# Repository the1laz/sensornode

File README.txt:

Wireless sensor node hardware designed for nRF24L01 radios.

Model A is a node for an Atmega328.

Tabs are addon boards that connect to one of the 10 pin headers.

More information and pictures can be found on my blog: http://www.addictedtopi.com

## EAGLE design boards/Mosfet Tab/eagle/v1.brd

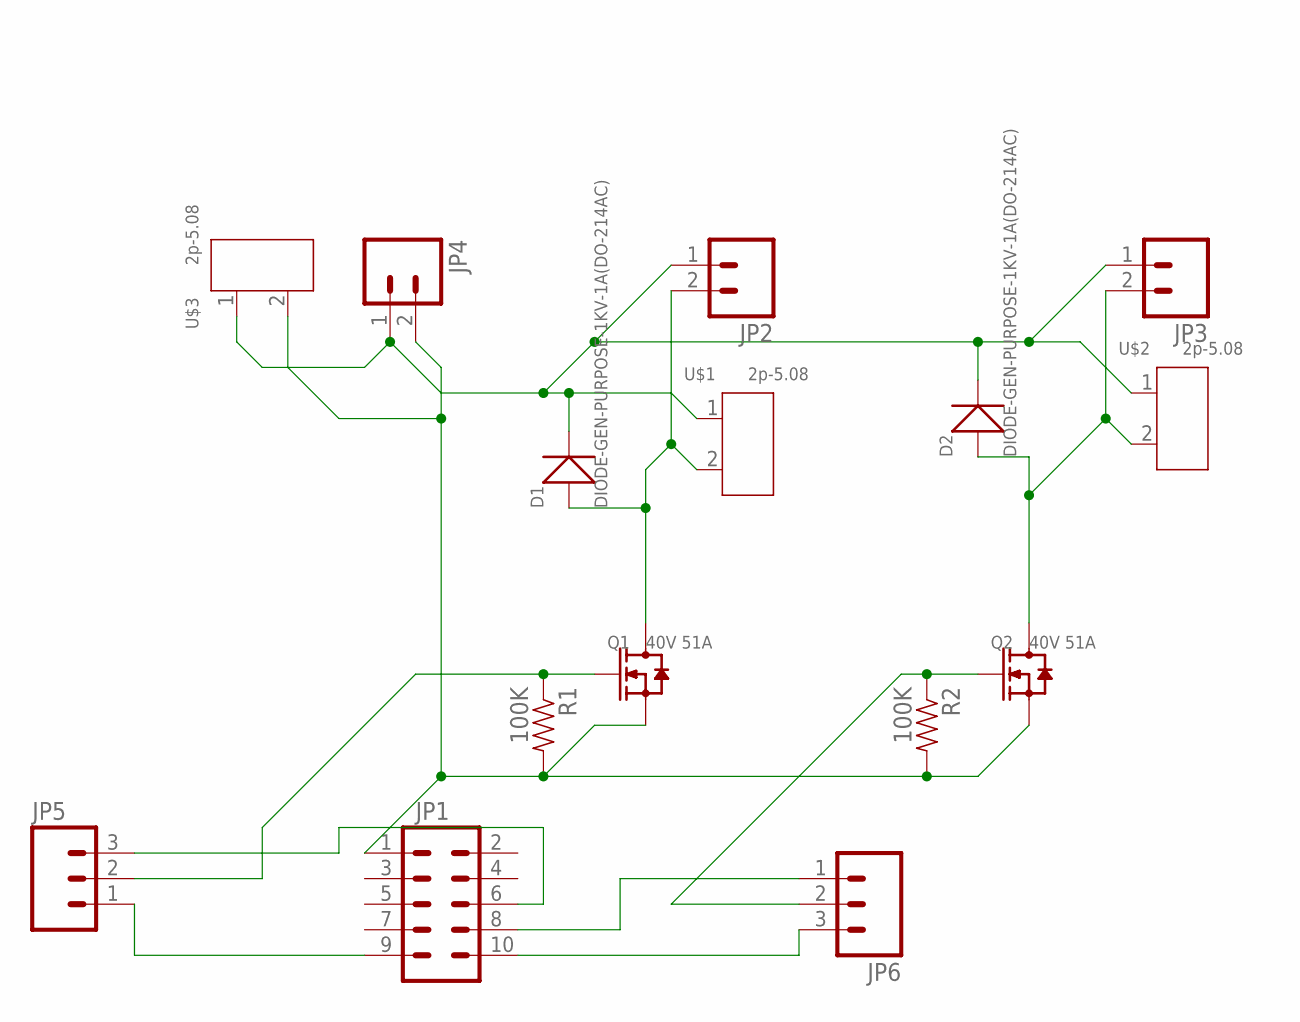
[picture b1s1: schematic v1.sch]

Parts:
D1, D2: DIODE-GEN-PURPOSE-1KV-1A(DO-214AC); DO-214AC
JP1: M05X2PTH; AVR_ICSP
JP2, JP3, JP4: M02POLAR; MOLEX-1X2
JP5, JP6: M03PTH; 1X03
Q1, Q2: 40V 51A; DPAK
R1, R2: 100K; 0805
U$1, U$2, U$3: 2p-5.08; H2-5.0-10.5X8.0MM

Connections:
GND: JP1.1, JP4.2, Q1.2 (S), Q2.2 (S), R1.2, R2.2, U$3.2
unnamed: D1.2 (-), D2.2 (-), JP2.1, JP3.1, JP4.1, U$1.1, U$2.1, U$3.1
unnamed: D2.1 (+), JP3.2, Q2.3 (D), U$2.2
unnamed: D1.1 (+), JP2.2, Q1.3 (D), U$1.2
unnamed: JP5.2, Q1.1 (G), R1.1
unnamed: JP6.2, Q2.1 (G), R2.1
unnamed: JP1.9, JP5.1
unnamed: JP1.10, JP6.3
unnamed: JP1.6, JP5.3
unnamed: JP1.8, JP6.1

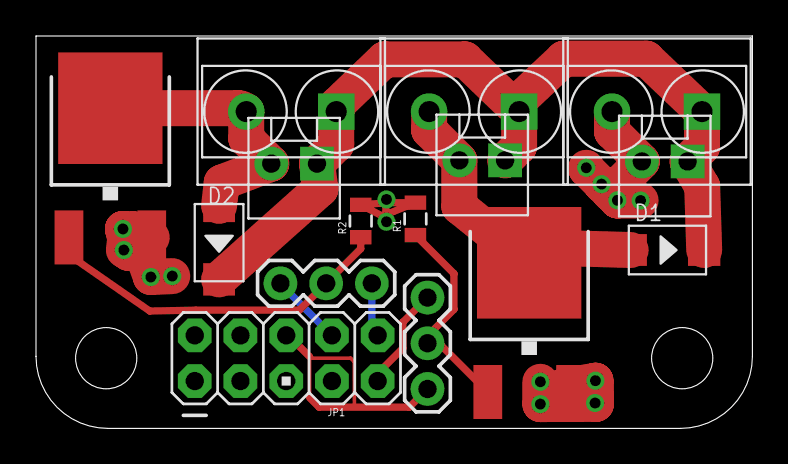
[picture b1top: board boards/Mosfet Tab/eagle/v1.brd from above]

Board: 2 copper layers, 39.8 x 21.8 mm, 15 parts (0 on the bottom side), 10 nets.

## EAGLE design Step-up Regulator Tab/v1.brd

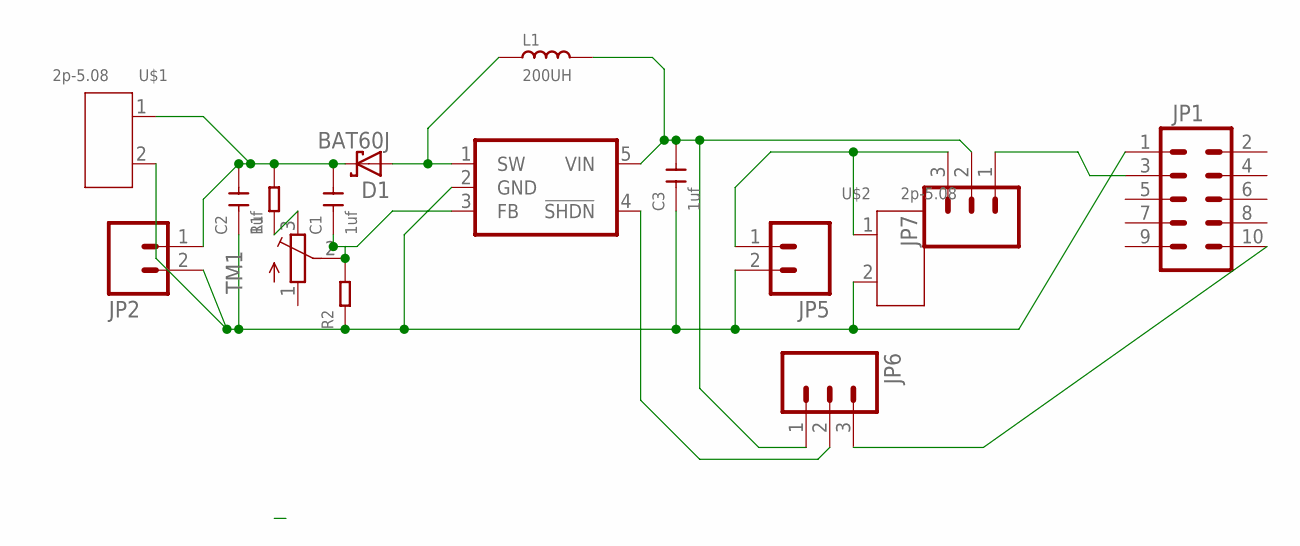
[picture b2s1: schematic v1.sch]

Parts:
C1, C2, C3: 1uf; C0805
D1: BAT60J; SOD323_ST
IC1: IC_FAN5331-SOT-23-5; SOT-23-5
JP1: M05X2PTH; AVR_ICSP
JP2, JP5: M02PTH; 1X02
JP6, JP7: M03PTH; 1X03
L1: 200UH; SMD-2P-5.0X5.0X2.0MM
R1, R2: RES-0805; R0805
TM1: TRIMPOTTC33X; TC33X
U$1, U$2: 2p-5.08; H2-5.0-10.5X8.0MM

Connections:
GND: C2.1, C3.1, IC1.2 (GND), JP1.1, JP2.2, JP5.2, R2.1, U$1.2, U$2.2
unnamed: JP1.3, JP7.1
unnamed: C3.2, IC1.5 (VIN), JP6.1, JP7.2, L1.2
unnamed: IC1.4 (!SHDN), JP6.2
unnamed: JP1.10, JP6.3
unnamed: D1.A, IC1.1 (SW), L1.1
unnamed: C1.2, C2.2, D1.C, JP2.1, R1.2, U$1.1
unnamed: C1.1, IC1.3 (FB), R2.2, TM1.2 (S)
unnamed: JP5.1, JP7.3, U$2.1
unnamed: R1.1, TM1.3 (E)

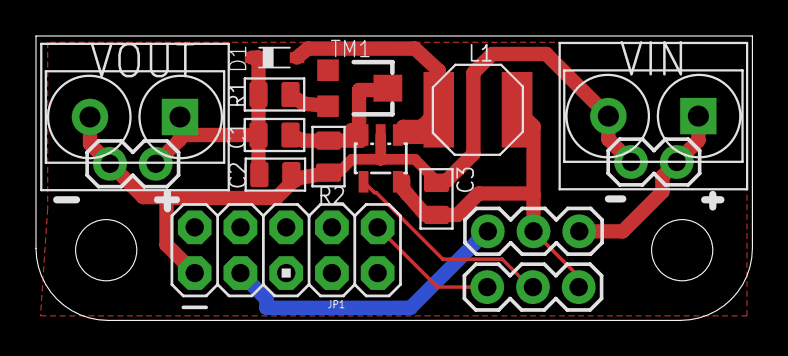
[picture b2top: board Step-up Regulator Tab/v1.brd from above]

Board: 2 copper layers, 39.8 x 15.8 mm, 16 parts (0 on the bottom side), 10 nets.

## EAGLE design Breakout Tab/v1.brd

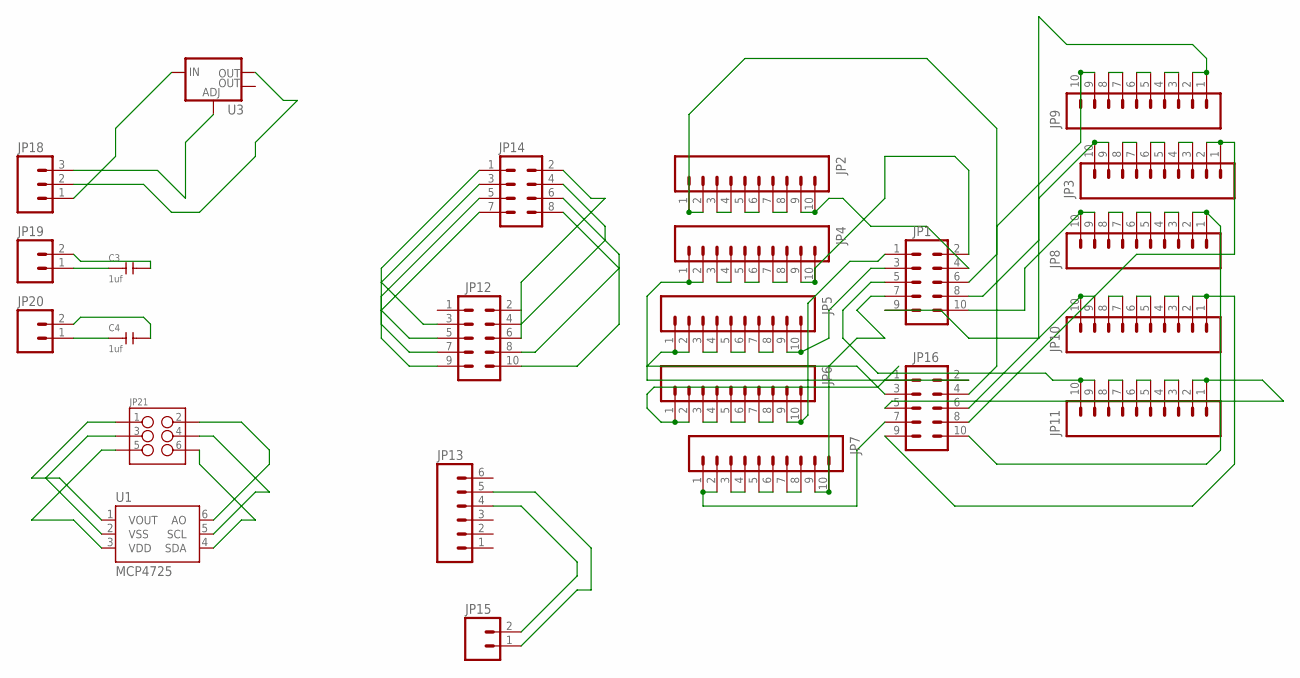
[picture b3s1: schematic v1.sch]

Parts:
C3, C4: 1uf; C0805
JP1, JP12, JP16: M05X2PTH; AVR_ICSP
JP2, JP3, JP4, JP5, JP6, JP7, JP8, JP9, JP10, JP11: M10SILK_FEMALE_PTH; 1X10
JP13: M06SILK_FEMALE_PTH; 1X06
JP14: M04X2; 2X4
JP15, JP19, JP20: M02PTH; 1X02
JP18: M03PTH; 1X03
JP21: M03X22X3_SILK_MALE_PTH; 2X3
U1: MCP4725; SOT23-6
U3: V_REG_LM1117SOT223; SOT223

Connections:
unnamed: JP2.3, JP2.4
unnamed: JP1.2, JP4.9, JP4.10
unnamed: JP1.3, JP5.9, JP5.10
unnamed: JP1.1, JP6.9, JP6.10
unnamed: JP1.9, JP10.9, JP10.10
unnamed: JP1.5, JP11.9, JP11.10
unnamed: JP3.1, JP3.2, JP16.8
unnamed: JP1.8, JP3.9, JP3.10
unnamed: JP1.7, JP7.9, JP7.10
unnamed: JP1.6, JP9.9, JP9.10
unnamed: JP9.7, JP9.8
unnamed: JP9.5, JP9.6
unnamed: JP9.3, JP9.4
unnamed: JP9.1, JP9.2, JP16.6
unnamed: JP3.7, JP3.8
unnamed: JP3.5, JP3.6
unnamed: JP3.3, JP3.4
unnamed: JP21.2, U1.6 (AO)
unnamed: JP10.1, JP10.2, JP16.9
unnamed: JP8.3, JP8.4
unnamed: JP8.5, JP8.6
unnamed: JP8.7, JP8.8
unnamed: JP11.7, JP11.8
unnamed: JP11.5, JP11.6
unnamed: JP11.3, JP11.4
unnamed: JP6.1, JP6.2, JP16.1
unnamed: JP21.4, U1.5 (SCL)
unnamed: JP10.3, JP10.4
unnamed: JP10.5, JP10.6
unnamed: JP10.7, JP10.8
unnamed: JP5.7, JP5.8
unnamed: JP5.5, JP5.6
unnamed: JP5.1, JP5.2, JP16.3
unnamed: JP5.3, JP5.4
unnamed: JP21.6, U1.4 (SDA)
unnamed: JP6.3, JP6.4
unnamed: JP6.5, JP6.6
unnamed: JP6.7, JP6.8
unnamed: JP7.1, JP7.2, JP16.7
unnamed: JP7.3, JP7.4
unnamed: JP7.5, JP7.6
unnamed: JP7.7, JP7.8
unnamed: JP4.1, JP4.2, JP16.2
unnamed: JP4.3, JP4.4
unnamed: JP4.5, JP4.6
unnamed: JP4.7, JP4.8
unnamed: JP11.1, JP11.2, JP16.5
unnamed: JP2.7, JP2.8
unnamed: JP2.5, JP2.6
unnamed: JP2.1, JP2.2, JP16.4
unnamed: JP1.10, JP8.9, JP8.10
unnamed: JP21.5, U1.3 (VDD)
unnamed: JP21.3, U1.2 (VSS)
unnamed: JP1.4, JP2.9, JP2.10
unnamed: JP13.4, JP15.2
unnamed: JP13.5, JP15.1
unnamed: JP12.4, JP14.2
unnamed: JP12.6, JP14.4
unnamed: JP12.8, JP14.6
unnamed: JP12.10, JP14.8
unnamed: JP12.3, JP14.1
unnamed: JP12.5, JP14.3
unnamed: JP12.7, JP14.5
unnamed: JP12.9, JP14.7
unnamed: JP21.1, U1.1 (VOUT)
unnamed: JP18.3, U3.1 (ADJ)
unnamed: JP8.1, JP8.2, JP16.10
unnamed: C3.1, JP19.1
unnamed: C3.2, JP19.2
unnamed: C4.1, JP20.1
unnamed: C4.2, JP20.2
unnamed: JP18.2, U3.2 (OUT)
unnamed: JP18.1, U3.3 (IN)

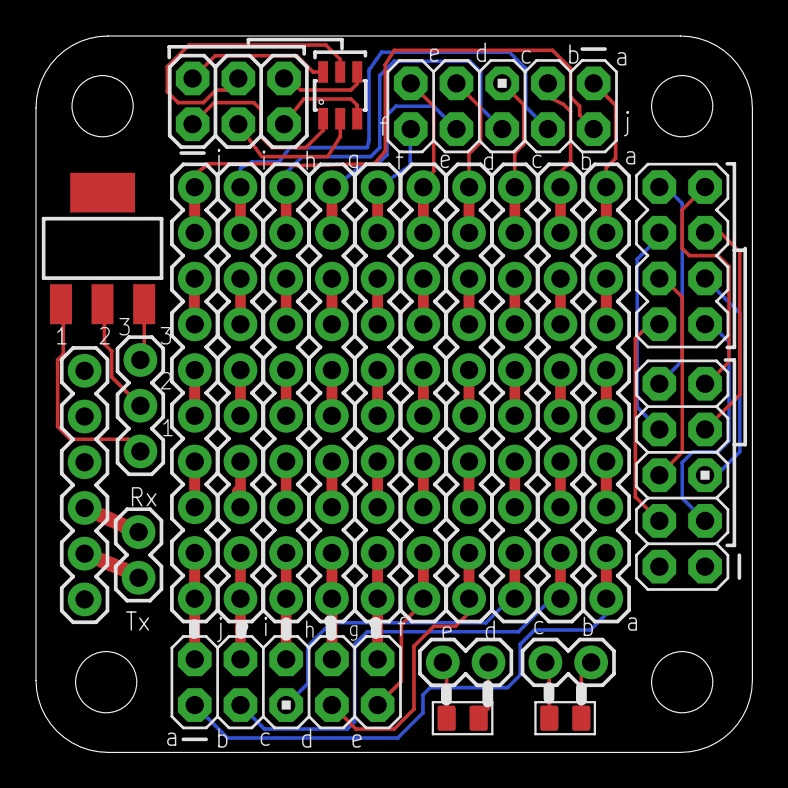
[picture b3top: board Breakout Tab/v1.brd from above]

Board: 2 copper layers, 39.8 x 39.8 mm, 24 parts (0 on the bottom side), 73 nets.

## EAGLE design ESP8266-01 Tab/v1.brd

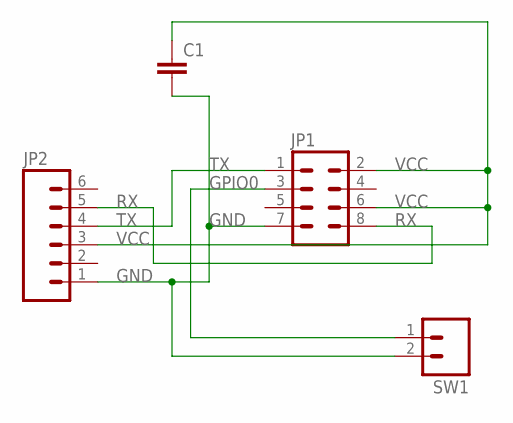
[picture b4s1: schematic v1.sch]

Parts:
C1: CAPPTH; CAP-PTH-SMALL
JP1: M04X2; 2X4
JP2: M06SILK_FEMALE_PTH; 1X06
SW1: M02PTH; 1X02

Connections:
GND: C1.2, JP1.7, JP2.1, SW1.2
GPIO0: JP1.3, SW1.1
RX: JP1.8, JP2.5
TX: JP1.1, JP2.4
VCC: C1.1, JP1.2, JP1.6, JP2.3

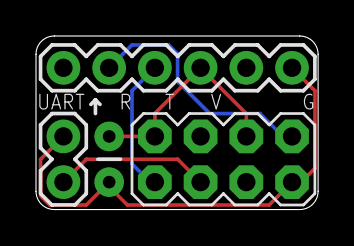
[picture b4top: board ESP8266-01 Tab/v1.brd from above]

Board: 2 copper layers, 15.7 x 9.6 mm, 4 parts (0 on the bottom side), 5 nets.

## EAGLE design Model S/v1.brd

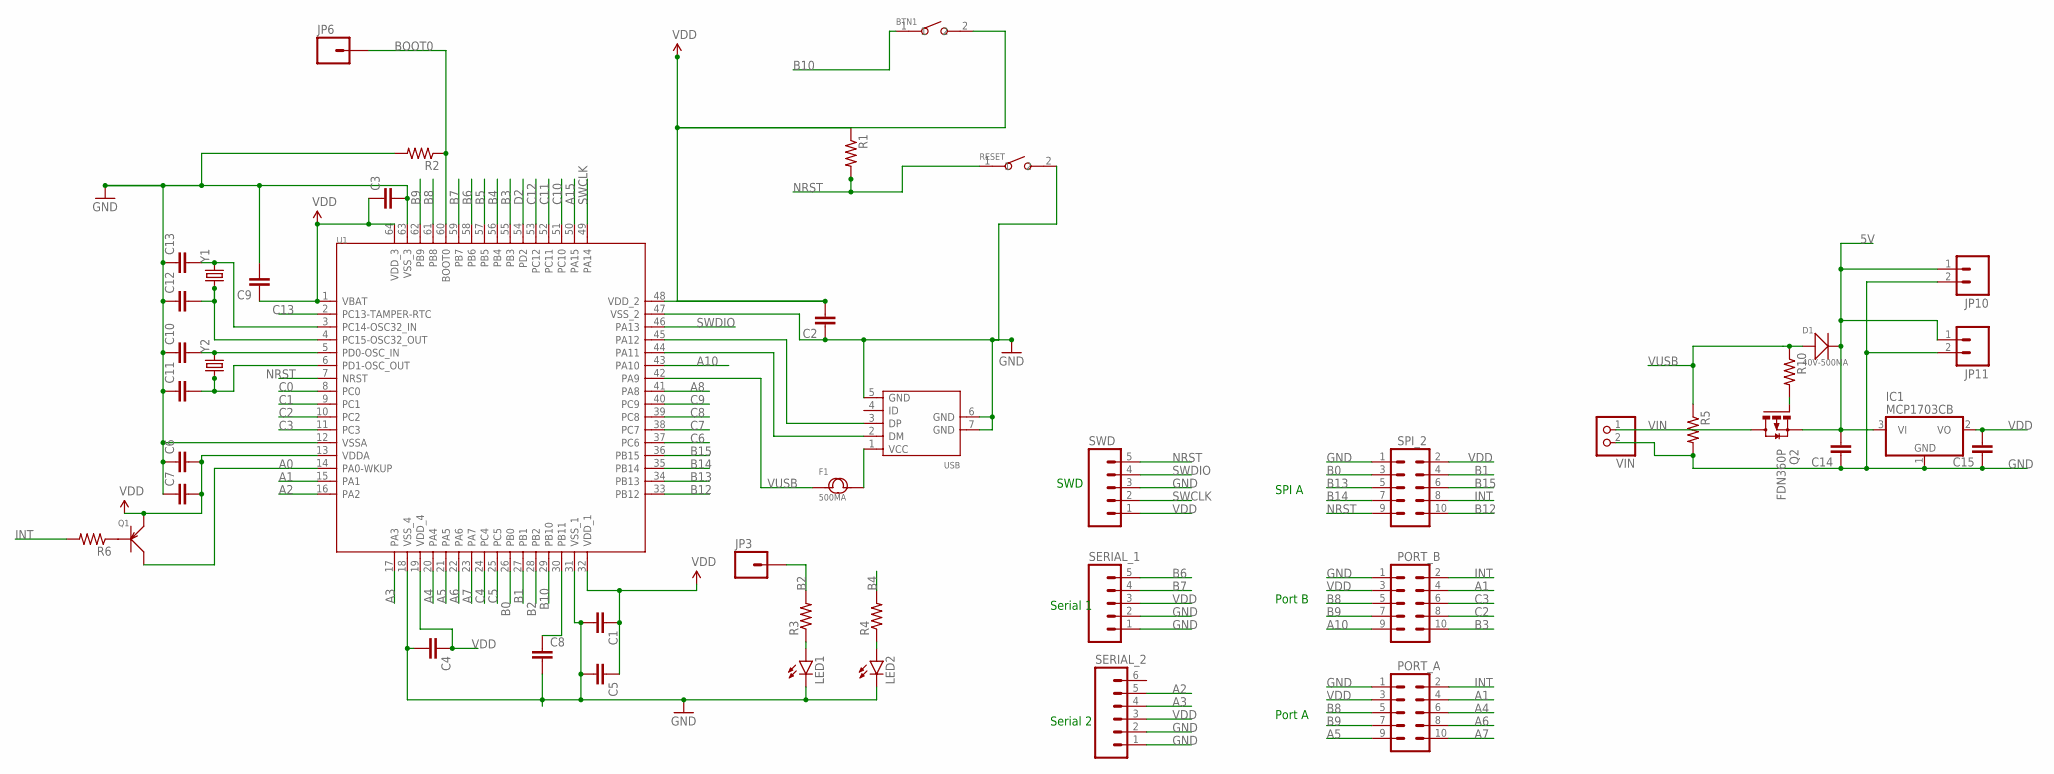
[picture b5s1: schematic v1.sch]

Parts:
BTN1: SMD-BUTTON(2P-6.0X3.0X2.5MM)-DHT-1163S; SW2-4.0-6.0X3.0X2.5MM
C1, C2, C3, C4, C5, C6, C7, C8, C9, C10, C11, C12, C13, C14, C15: CAP0805; 0805
D1: 40V-500MA; SOD-123
F1: 500MA; F1206
IC1: MCP1703CB; SOT23
JP3, JP6: M01NOSILK-KIT; 1X01NS-KIT
JP10, JP11: M02PTH; 1X02
LED1, LED2: LED1206; LED-1206
PORT_A: M05X2PTH; AVR_ICSP
PORT_B: M05X2PTH; AVR_ICSP
Q1: SMD-TRANSISTORS-PNP-25V-500MA(SOT-23); SOT-23
Q2: FDN360P; SUPER-SOT3
R1, R2, R3, R4, R5, R6, R10: RESISTOR0805-RES; 0805
RESET: SMD-BUTTON(2P-6.0X3.0X2.5MM)-DHT-1163S; SW2-4.0-6.0X3.0X2.5MM
SERIAL_1: M051.27MM; 1X05-1.27MM
SERIAL_2: M06SILK_FEMALE_PTH; 1X06
SPI_2: M05X2PTH; AVR_ICSP
SWD: M051.27MM; 1X05-1.27MM
U1: MCU-STM32F401RBT6(LQFP64); LQFP64-0.5-10X10MM
USB: MICRO-USB-SMD-TYPE-AB-R/A(ST-USB-001L); MICRO-USB5+2P-SMD-0.65
VIN: JST_2PIN-SMT-RA; JST-PH-2-SMT-RA
Y1, Y2: CRYSTAL5X3; CRYSTAL-SMD-5X3

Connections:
5V: C14.2, D1.-, IC1.3 (VI), JP10.1, JP11.1, Q2.2 (S)
A0: Q1.3 (C), U1.14 (PA0-WKUP)
A1: PORT_A.4, PORT_B.4, U1.15 (PA1)
A2: SERIAL_2.5, U1.16 (PA2)
A3: SERIAL_2.4, U1.17 (PA3)
A4: PORT_A.6, U1.20 (PA4)
A5: PORT_A.9, U1.21 (PA5)
A6: PORT_A.8, U1.22 (PA6)
A7: PORT_A.10, U1.23 (PA7)
A8: U1.41 (PA8)
A10: PORT_B.9, U1.43 (PA10)
A15: U1.50 (PA15)
B0: SPI_2.3, U1.26 (PB0)
B1: SPI_2.4, U1.27 (PB1)
B2: JP3.1, R3.2, U1.28 (PB2)
B3: PORT_B.10, U1.55 (PB3)
B4: R4.2, U1.56 (PB4)
B5: U1.57 (PB5)
B6: SERIAL_1.5, U1.58 (PB6)
B7: SERIAL_1.4, U1.59 (PB7)
B8: PORT_A.5, PORT_B.5, U1.61 (PB8)
B9: PORT_A.7, PORT_B.7, U1.62 (PB9)
B10: BTN1.1, U1.29 (PB10)
B12: SPI_2.10, U1.33 (PB12)
B13: SPI_2.5, U1.34 (PB13)
B14: SPI_2.7, U1.35 (PB14)
B15: SPI_2.6, U1.36 (PB15)
BOOT0: JP6.1, R2.1, U1.60 (BOOT0)
C0: U1.8 (PC0)
C1: U1.9 (PC1)
C2: PORT_B.8, U1.10 (PC2)
C3: PORT_B.6, U1.11 (PC3)
C4: U1.24 (PC4)
C5: U1.25 (PC5)
C6: U1.37 (PC6)
C7: U1.38 (PC7)
C8: U1.39 (PC8)
C9: U1.40 (PC9)
C10: U1.51 (PC10)
C11: U1.52 (PC11)
C12: U1.53 (PC12)
C13: U1.2 (PC13-TAMPER-RTC)
D2: U1.54 (PD2)
GND: C1.2, C2.1, C3.2, C4.2, C5.2, C6.1, C7.1, C8.2, C9.2, C10.1, C11.1, C12.1, C13.1, C14.1, C15.1, IC1.1 (GND), JP10.2, JP11.2, LED1.C, LED2.C, PORT_A.1, PORT_B.1, R2.2, R5.2, RESET.2, SERIAL_1.1, SERIAL_1.2, SERIAL_2.1, SERIAL_2.2, SPI_2.1, SWD.3, U1.12 (VSSA), U1.18 (VSS_4), U1.31 (VSS_1), U1.47 (VSS_2), U1.63 (VSS_3), USB.5 (GND), USB.6 (GND), USB.7 (GND), VIN.2 (1)
INT: PORT_A.2, PORT_B.2, R6.2, SPI_2.8
unnamed: C13.2, U1.3 (PC14-OSC32_IN), Y1.3 (2)
unnamed: C8.1, U1.30 (PB11)
unnamed: C12.2, U1.4 (PC15-OSC32_OUT), Y1.1
unnamed: C10.2, U1.5 (PD0-OSC_IN), Y2.3 (2)
unnamed: C11.2, U1.6 (PD1-OSC_OUT), Y2.1
unnamed: U1.44 (PA11), USB.2 (DM)
unnamed: U1.45 (PA12), USB.3 (DP)
unnamed: Q1.1 (B), R6.1
unnamed: F1.2, USB.1 (VCC)
unnamed: LED1.A, R3.1
unnamed: LED2.A, R4.1
unnamed: Q2.1 (G), R10.2
NRST: R1.2, RESET.1, SPI_2.9, SWD.5, U1.7 (NRST)
SWCLK: SWD.2, U1.49 (PA14)
SWDIO: SWD.4, U1.46 (PA13)
VDD: BTN1.2, C1.1, C2.2, C3.1, C4.1, C5.1, C6.2, C7.2, C9.1, C15.2, IC1.2 (VO), PORT_A.3, PORT_B.3, Q1.2 (E), R1.1, SERIAL_1.3, SERIAL_2.3, SPI_2.2, SWD.1, U1.1 (VBAT), U1.13 (VDDA), U1.19 (VDD_4), U1.32 (VDD_1), U1.48 (VDD_2), U1.64 (VDD_3)
VIN: Q2.3 (D), VIN.1 (2)
VUSB: D1.+, F1.1, R5.1, R10.1, U1.42 (PA9)

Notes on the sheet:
Serial 1
Serial 2
SWD
Port A
Port B
SPI A

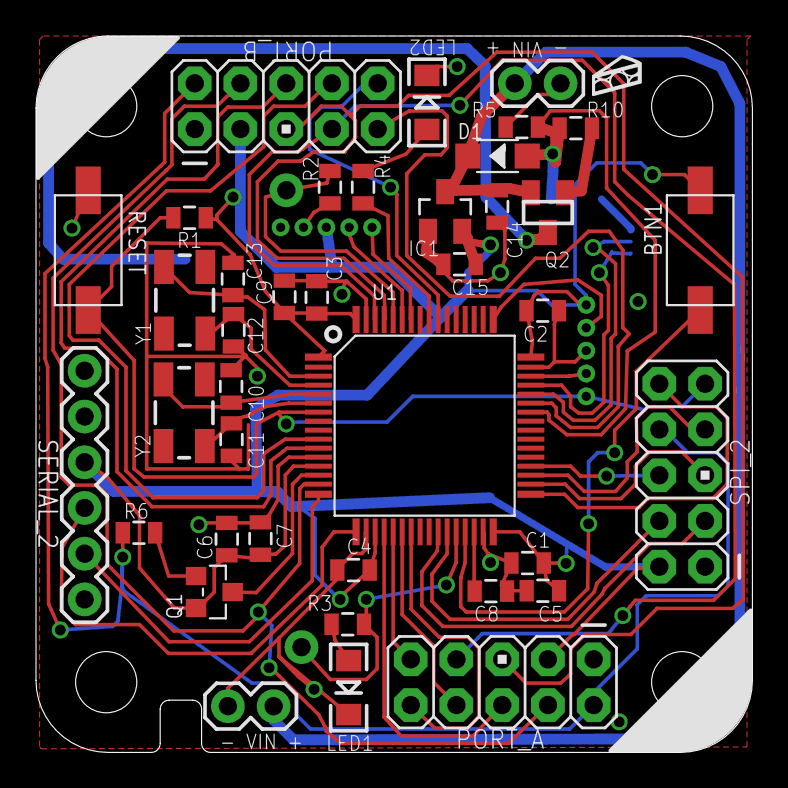
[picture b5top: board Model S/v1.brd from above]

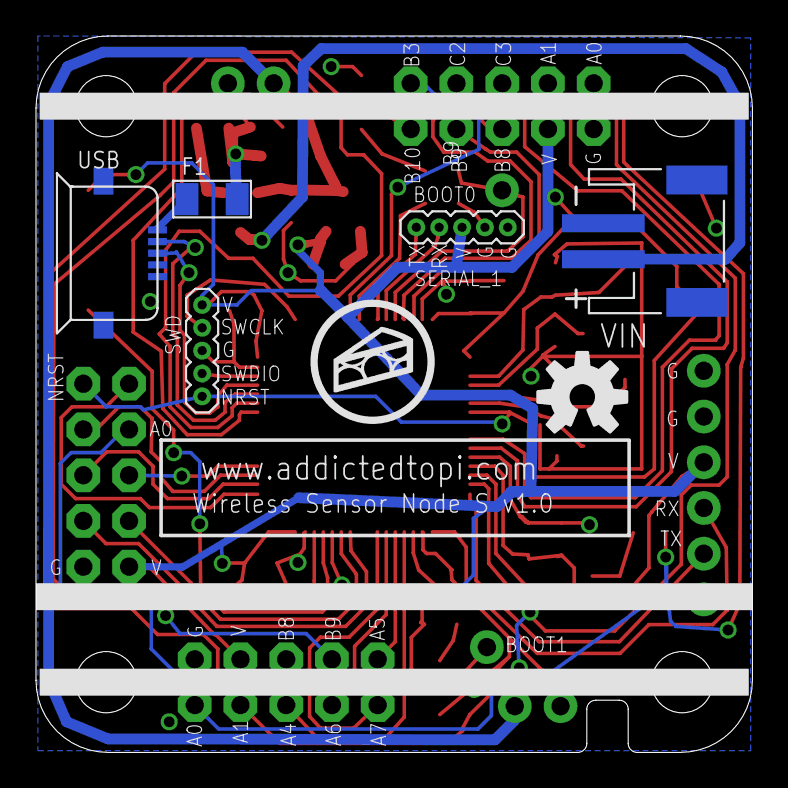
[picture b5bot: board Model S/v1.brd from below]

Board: 2 copper layers, 39.8 x 39.8 mm, 49 parts (7 on the bottom side), 47 nets.

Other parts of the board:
U$1: PI
U$2: OSHW-LOGO-M
U$3: PI_XS

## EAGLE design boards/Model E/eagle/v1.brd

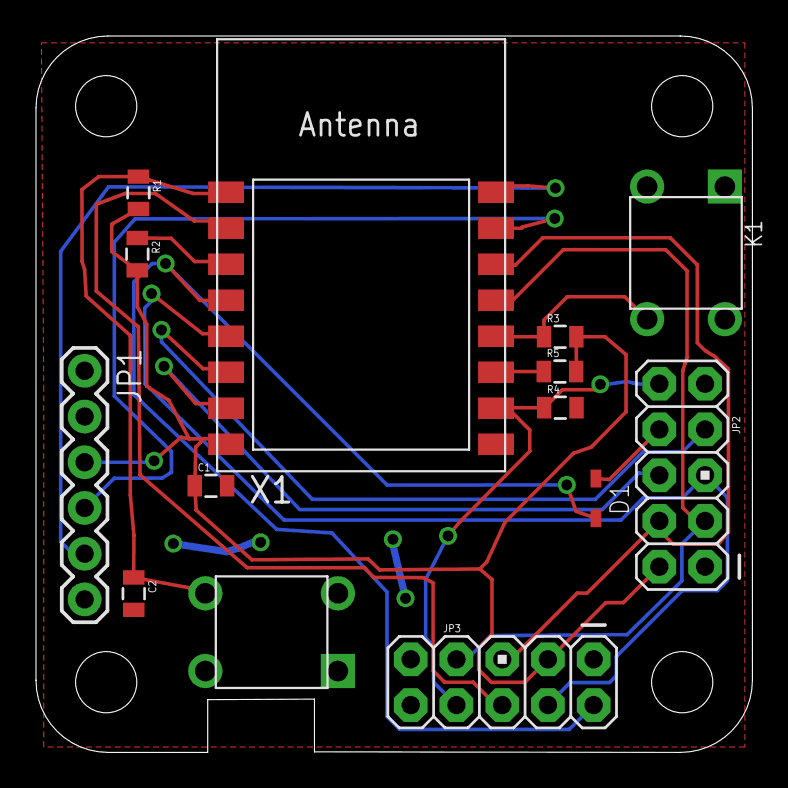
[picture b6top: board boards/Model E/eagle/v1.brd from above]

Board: 2 copper layers, 39.8 x 39.8 mm, 14 parts (0 on the bottom side), 17 nets.

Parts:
C1, C2: 0805
D1: SOD323
JP1: 1X06
JP2, JP3: AVR_ICSP
K1, K2: TS-1109; SW4-6.0X6.0X5.0MM
R1, R2, R3, R4, R5: 0805
X1: ESP-12

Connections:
ADC: JP3.6, X1.2
GND: C1.2, C2.2, JP1.1, JP1.2, JP2.1, JP3.1, K1.4, K2.4, R4.2, X1.9
GPIO0: K1.3, R3.1, X1.12
GPIO2: R5.1, X1.11
GPIO4: JP2.3, JP3.7, X1.13
GPIO5: JP2.4, JP3.5, X1.14
GPIO14: JP2.5, JP3.4, X1.5
GPIO16: D1.2, JP3.2, X1.4
unnamed: JP1.5, X1.16
unnamed: JP1.4, X1.15
unnamed: JP2.7, X1.6
unnamed: JP2.6, X1.7
unnamed: D1.1, JP2.8
unnamed: C2.1, K2.3, R1.1, X1.1
unnamed: R2.1, X1.3
SPI_CS: JP2.10, JP3.8, R4.1, X1.10
VCC: C1.1, JP1.3, JP2.2, JP3.3, R1.2, R2.2, R3.2, R5.2, X1.8

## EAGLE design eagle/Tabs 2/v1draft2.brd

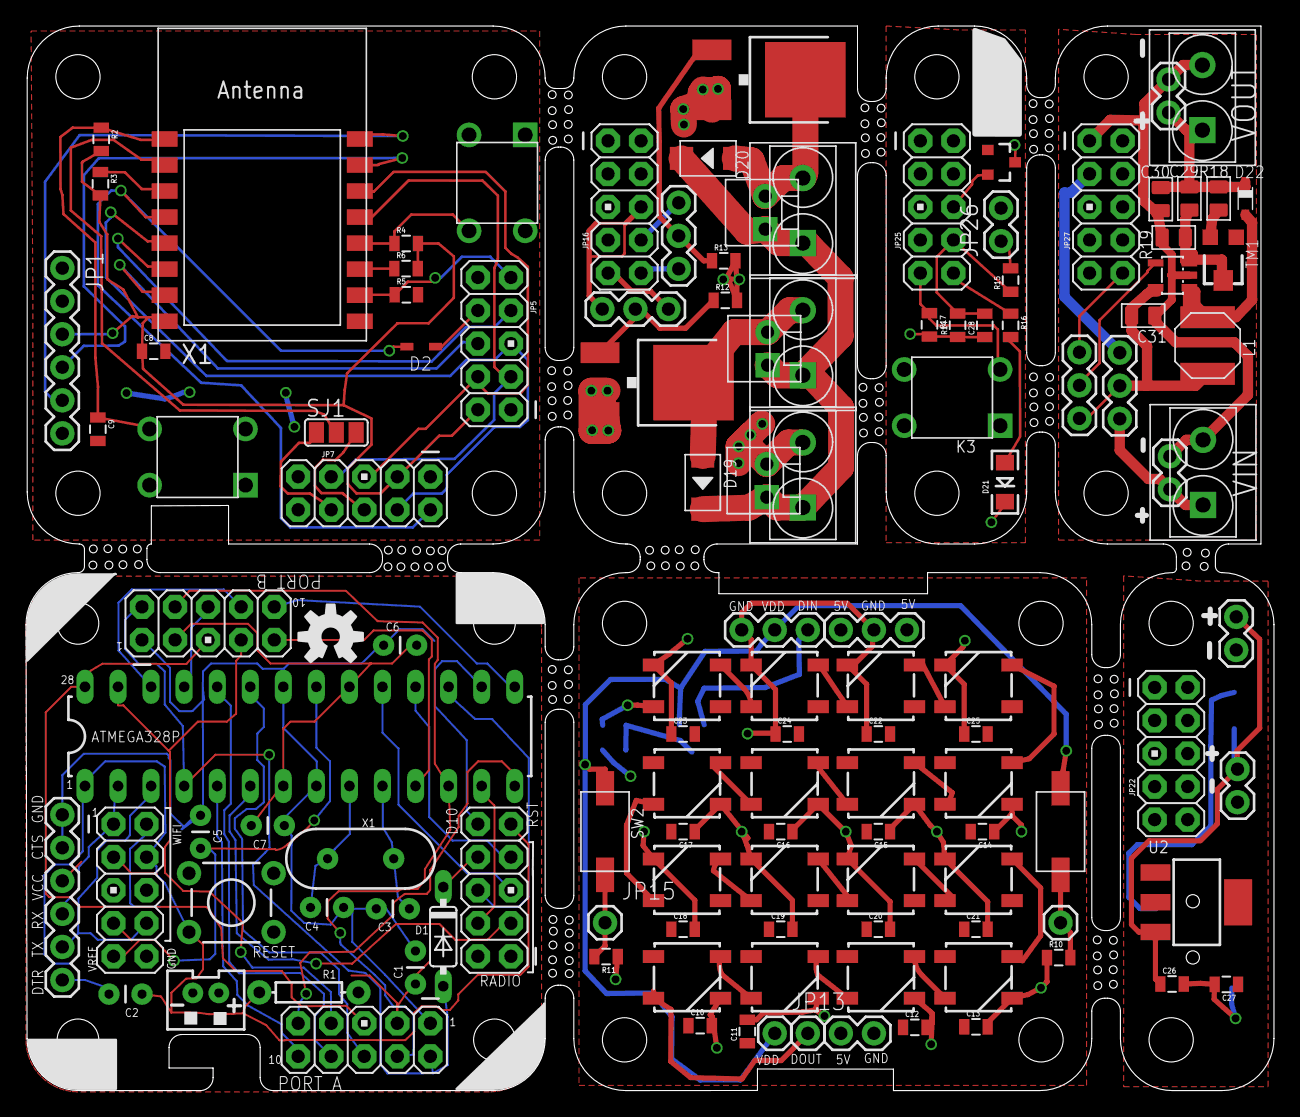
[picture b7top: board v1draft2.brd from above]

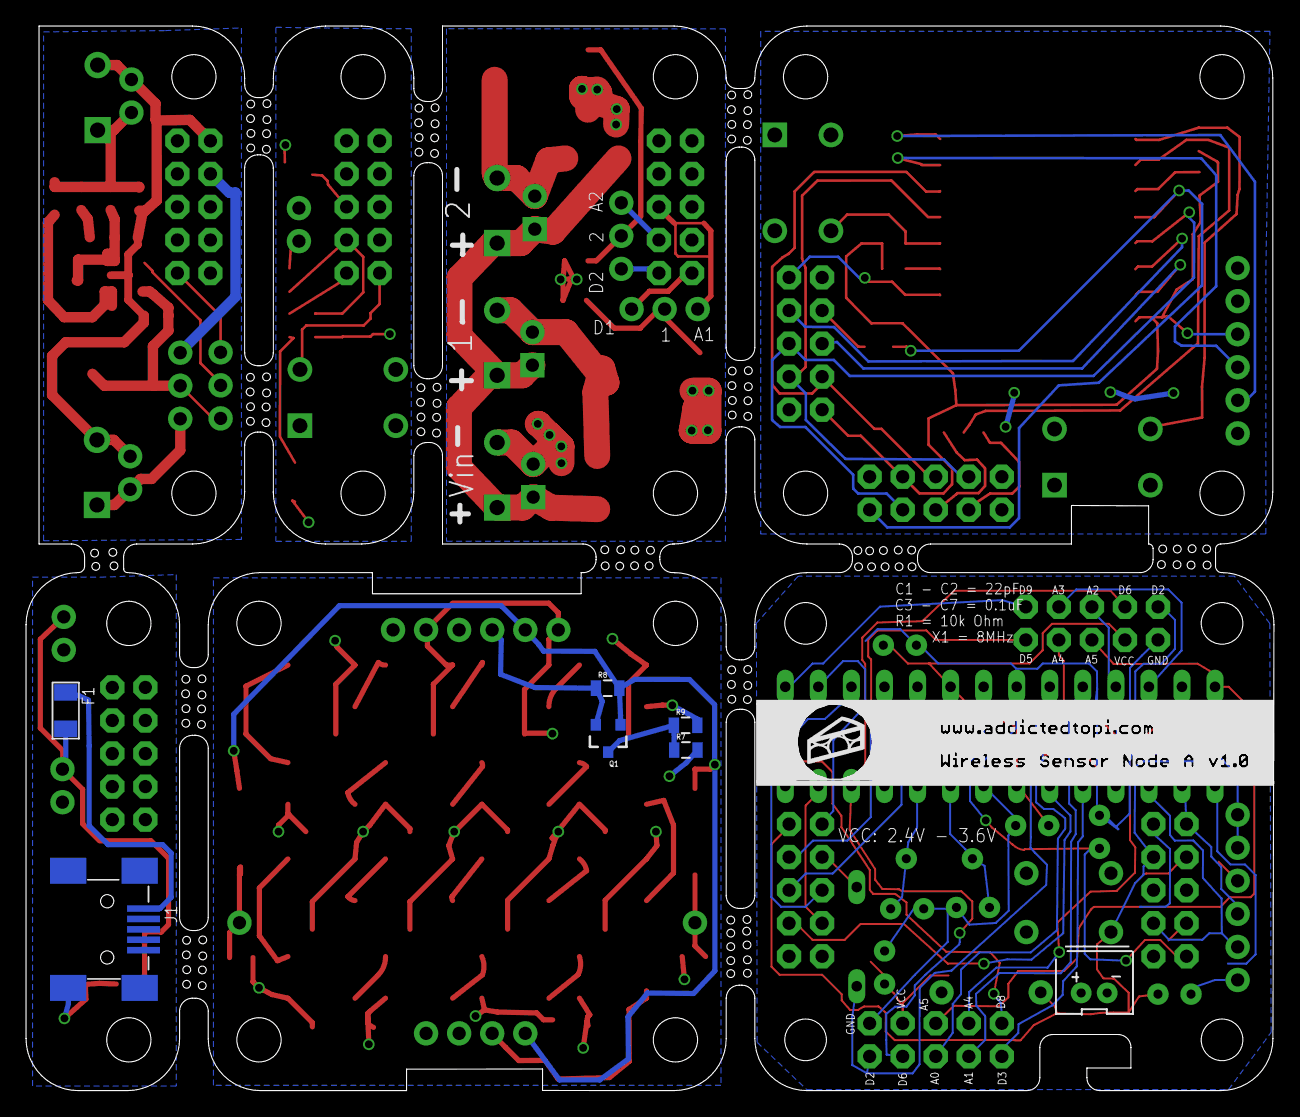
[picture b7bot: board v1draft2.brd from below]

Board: 2 copper layers, 95.9 x 81.8 mm, 132 parts (6 on the bottom side), 103 nets.

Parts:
C1, C2, C3, C4, C5, C6, C7: CAP-PTH-SMALL
C8, C9, C10, C11, C12, C13, C14, C15, C16, C17, C18, C19, C20, C21, C22, C23, C24, C25, C26, C27, C28: 0805
C29, C30, C31: 1uf; C0805
D1: 1N4148DO35-7; DO35-7
D2: SOD323
D3, D4, D5, D6, D7, D8, D9, D10, D11, D12, D13, D14, D15, D16, D17, D18: WS2812B
D19, D20: DIODE-GEN-PURPOSE-1KV-1A(DO-214AC); DO-214AC
D21: LED-1206
D22: BAT60J; SOD323_ST
F1: 500MA; F1206
IC1: IC_FAN5331-SOT-23-5; SOT-23-5
J1: MINIUSB5+4P-SMD-0.8-90D
JP1, JP4: 1X06
JP2, JP3, JP8: M05X2PTH; AVR_ICSP
JP5, JP7, JP16, JP22, JP25, JP27: AVR_ICSP
JP6: M02JST-PTH-VERT; JST-2-PTH-VERT
JP9, JP12, JP20, JP21, JP30, JP31: 1X03
JP10, JP13, JP14, JP15: 1X01
JP11, JP23, JP24, JP26, JP28, JP29: 1X02
JP17, JP18, JP19: MOLEX-1X2
K1, K2, K3: TS-1109; SW4-6.0X6.0X5.0MM
L1: 200UH; SMD-2P-5.0X5.0X2.0MM
Q1: 200mA/50V; SOT23-3
Q2, Q3: 40V 51A; DPAK
R1: AXIAL-0.3
R2, R3, R4, R5, R6, R7, R8, R9, R10, R11, R12, R13, R14, R15, R16, R17: 0805
R18, R19: R0805
RESET: SWITCH-MOMENTARY-2PTH; TACTILE-PTH
RF24: M05X2PTH; AVR_ICSP
SJ1: JUMPER-PAD-3-NOYES_SILK; PAD-JUMPER-3-NO_YES_SILK_FULL_BOX
SW1, SW2: SW2-4.0-6.0X3.0X2.5MM
TM1: TC33X
U1: ATMEGA328P_PDIP; DIL28-3
U2: PMIC-CJT1117-3.3(SOT223); SOT-223
U$1: DP4040_V1_NOLINES
U$2, U$3, U$4, U$8, U$9: 2p-5.08; H2-5.0-10.5X8.0MM
U$5: PI
U$6: OSHW-LOGO-M
U$7: MCP9700SMD; SOT23-3
X1: ESP-12
Y1: HC49US

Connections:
3.3V: JP9.2, JP13.1, Q1.1, R8.2, SW1.1, SW2.1
ADC: SJ1.2, X1.2
DIN: JP9.3, Q1.2, R8.1
GND: C1.2, C2.2, C3.2, C5.2, C6.2, C7.2, JP2.1, JP3.1, JP4.1, JP4.2, JP6.2, JP8.2, JP8.10, RESET.1, RF24.1, U1.8, U1.22
GND1: C8.2, C9.2, JP1.1, JP1.2, JP5.1, JP7.1, K1.4, K2.4, R5.2, X1.9
GND2: JP16.1, JP19.2, Q2.2, Q3.2, R12.2, R13.2, U$4.2
GND3: C26.2, C27.2, J1.5, J1.P$1, J1.P$2, J1.P$3, J1.P$4, JP22.1, JP23.2, JP24.2, U2.1
GND4: C28.1, D21.C, JP25.1, R14.1, R17.2, U$7.3
GND5: C30.1, C31.1, IC1.2, JP27.1, JP28.2, JP29.2, R19.1, U$8.2, U$9.2
GPIO0: K1.3, R4.1, X1.12
GPIO2: R6.1, X1.11
GPIO4: JP5.3, JP7.7, X1.13
GPIO5: JP5.4, JP7.5, X1.14
GPIO14: JP5.5, JP7.4, X1.5
GPIO16: D2.2, JP7.2, X1.4
unnamed: C2.1, U1.9, Y1.2
unnamed: C4.1, JP8.4, R1.P$2, RESET.3, RF24.9, U1.1
unnamed: C1.1, U1.10, Y1.1
unnamed: RF24.10, U1.16
unnamed: JP2.4, JP3.4, U1.12
unnamed: C5.1, JP8.9, U1.21
unnamed: JP1.5, X1.16
unnamed: JP1.4, X1.15
unnamed: JP3.9, U1.14
unnamed: D1.A, JP2.2, JP3.2, U1.4
unnamed: JP3.6, U1.23
unnamed: JP3.8, U1.24
unnamed: C4.2, JP4.6
unnamed: JP2.6, U1.25
unnamed: JP2.8, U1.26
unnamed: RF24.6, U1.17
unnamed: JP3.10, U1.5
unnamed: JP4.5, JP8.8, U1.3
unnamed: JP4.4, JP8.1, U1.2
unnamed: RF24.4, U1.13
unnamed: JP2.5, JP3.5, U1.28
unnamed: JP2.7, JP3.7, U1.27
unnamed: RF24.5, U1.19
unnamed: D1.C, RF24.8
unnamed: RF24.3, U1.6
unnamed: RF24.7, U1.18
unnamed: JP2.10, U1.15
unnamed: JP2.9, U1.11
unnamed: JP5.7, X1.6
unnamed: JP5.6, X1.7
unnamed: JP7.6, SJ1.3
unnamed: JP7.8, SJ1.1
unnamed: D2.1, JP5.8
unnamed: C9.1, K2.3, R2.1, X1.1
unnamed: R3.1, X1.3
unnamed: D5.4, D6.2
unnamed: D4.4, D5.2
unnamed: D3.4, D4.2
unnamed: D11.4, D12.2
unnamed: D10.4, D11.2
unnamed: D10.2, D18.4
unnamed: D6.4, D13.2
unnamed: D7.2, D12.4
unnamed: D3.2, D17.4
unnamed: D9.4, D17.2
unnamed: D8.4, D9.2
unnamed: D7.4, D8.2
unnamed: D15.4, D16.2
unnamed: D14.4, D15.2
unnamed: D13.4, D14.2
unnamed: D16.4, R9.2
unnamed: D18.2, JP10.1
unnamed: Q1.3, R7.1, R9.1
unnamed: JP14.1, R10.2, SW1.2
unnamed: JP15.1, R11.2, SW2.2
unnamed: D19.2, D20.2, JP17.1, JP18.1, JP19.1, U$2.1, U$3.1, U$4.1
unnamed: D20.1, JP18.2, Q3.3, U$3.2
unnamed: D19.1, JP17.2, Q2.3, U$2.2
unnamed: JP20.2, Q2.1, R12.1
unnamed: JP21.2, Q3.1, R13.1
unnamed: JP16.9, JP20.1
unnamed: JP16.10, JP21.3
unnamed: JP16.6, JP20.3
unnamed: JP16.8, JP21.1
unnamed: C26.1, F1.2, JP23.1, JP24.1, U2.3
unnamed: F1.1, J1.1
unnamed: JP25.9, K3.2, R17.1
unnamed: D21.A, R16.2
unnamed: JP25.10, R16.1
unnamed: JP25.6, U$7.2
unnamed: C28.2, JP25.8, R14.2, R15.1
unnamed: JP26.1, R15.2
unnamed: JP27.3, JP31.1
unnamed: C31.2, IC1.5, JP30.1, JP31.2, L1.2
unnamed: IC1.4, JP30.2
unnamed: JP27.10, JP30.3
unnamed: D22.A, IC1.1, L1.1
unnamed: C29.2, C30.2, D22.C, JP28.1, R18.2, U$8.1
unnamed: C29.1, IC1.3, R19.2, TM1.2
unnamed: JP29.1, JP31.3, U$9.1
unnamed: R18.1, TM1.3
SPI_CS: JP5.9, R5.1, X1.10
VCC: C3.1, C6.1, C7.1, JP2.3, JP3.3, JP4.3, JP6.1, JP8.3, JP8.7, R1.P$1, RF24.2, U1.7, U1.20
VCC1: C8.1, JP1.3, JP5.2, JP7.3, R2.2, R3.2, R4.2, R6.2, X1.8
VDD: C10.1, C11.1, C12.1, C13.1, C14.2, C15.2, C16.2, C17.2, C18.1, C19.1, C20.1, C21.1, C22.2, C25.2, D3.1, D4.1, D5.1, D6.1, D7.1, D8.1, D9.1, D10.1, D11.1, D12.1, D13.1, D14.1, D15.1, D16.1, D17.1, D18.1, JP11.2, JP12.1, JP12.3, R7.2
VDD1: C27.1, JP22.3, U2.2, U2.TER
VDD2: JP25.3, JP26.2, K3.1, U$7.1
VSS: C10.2, C11.2, C12.2, C13.2, C14.1, C15.1, C16.1, C17.1, C18.2, C19.2, C20.2, C21.2, C22.1, C23.1, C24.1, C25.1, D3.3, D4.3, D5.3, D6.3, D7.3, D8.3, D9.3, D10.3, D11.3, D12.3, D13.3, D14.3, D15.3, D16.3, D17.3, D18.3, JP9.1, JP11.1, JP12.2, R10.1, R11.1

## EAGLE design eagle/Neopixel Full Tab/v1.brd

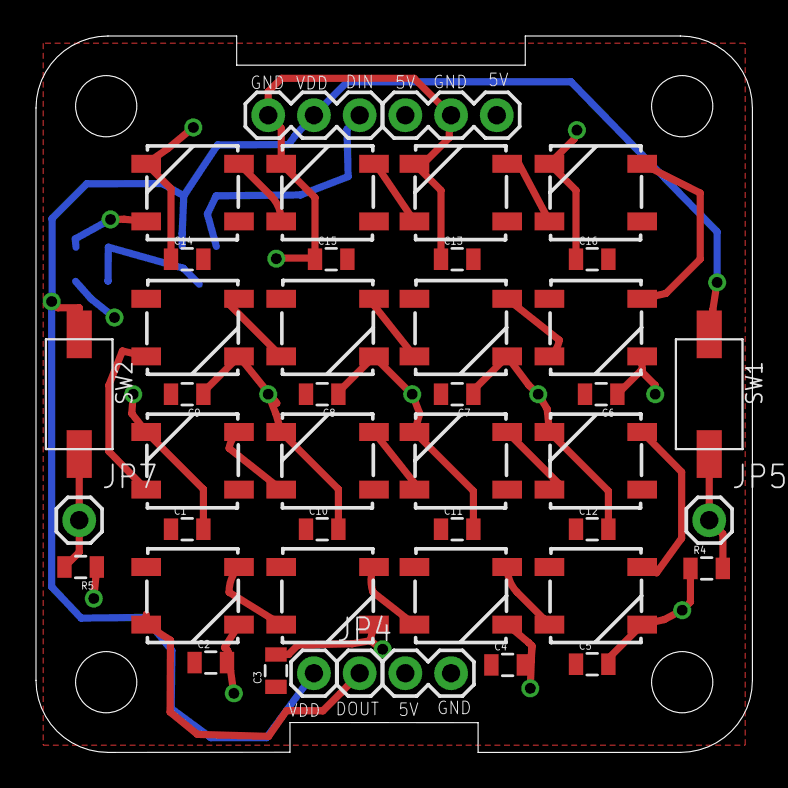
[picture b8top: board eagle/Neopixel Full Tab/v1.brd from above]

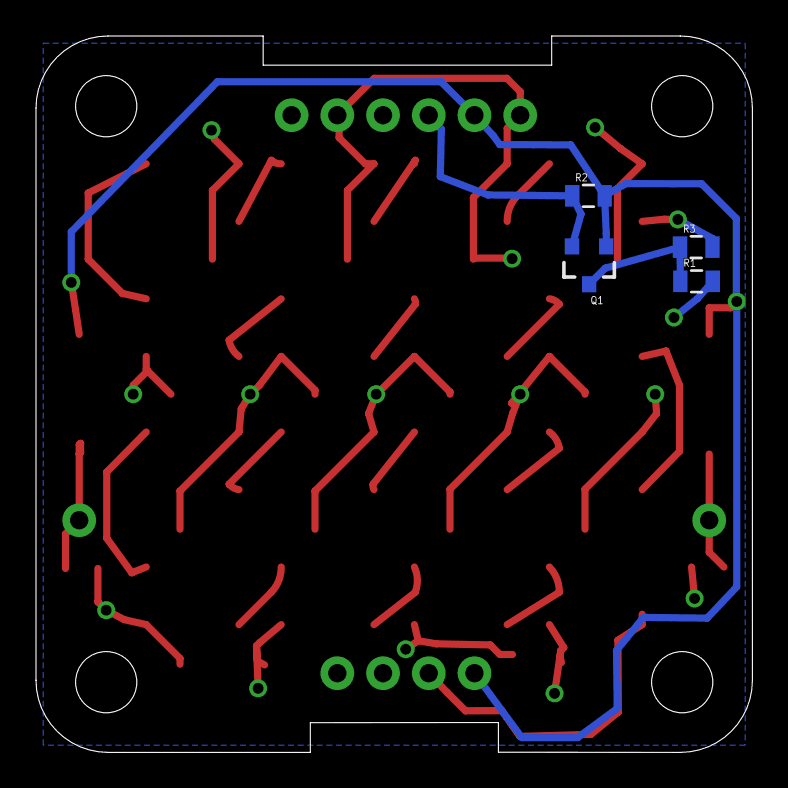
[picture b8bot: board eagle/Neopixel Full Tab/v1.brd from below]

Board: 2 copper layers, 39.8 x 39.8 mm, 47 parts (4 on the bottom side), 24 nets.

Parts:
C1, C2, C3, C4, C5, C6, C7, C8, C9, C10, C11, C12, C13, C14, C15, C16: 0805
D1, D2, D3, D4, D5, D6, D7, D8, D9, D10, D11, D12, D13, D14, D15, D16: WS2812B
JP1, JP4, JP5, JP7: 1X01
JP2, JP3: 1X03
JP6: 1X02
Q1: 200mA/50V; SOT23-3
R1, R2, R3, R4, R5: 0805
SW1, SW2: SW2-4.0-6.0X3.0X2.5MM

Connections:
3.3V: JP3.2, JP4.1, Q1.1, R2.2, SW1.1, SW2.1
DIN: JP3.3, Q1.2, R2.1
unnamed: D3.4, D4.2
unnamed: D2.4, D3.2
unnamed: D1.4, D2.2
unnamed: D11.4, D12.2
unnamed: D10.4, D11.2
unnamed: D9.4, D10.2
unnamed: D4.4, D13.2
unnamed: D5.2, D12.4
unnamed: D1.2, D8.4
unnamed: D7.4, D8.2
unnamed: D6.4, D7.2
unnamed: D5.4, D6.2
unnamed: D15.4, D16.2
unnamed: D14.4, D15.2
unnamed: D13.4, D14.2
unnamed: D9.2, JP1.1
unnamed: D16.4, R3.2
unnamed: Q1.3, R1.1, R3.1
unnamed: JP5.1, R4.2, SW1.2
unnamed: JP7.1, R5.2, SW2.2
VDD: C1.1, C2.1, C3.1, C4.1, C5.1, C6.2, C7.2, C8.2, C9.2, C10.1, C11.1, C12.1, C13.2, C16.2, D1.1, D2.1, D3.1, D4.1, D5.1, D6.1, D7.1, D8.1, D9.1, D10.1, D11.1, D12.1, D13.1, D14.1, D15.1, D16.1, JP2.1, JP2.3, JP6.2, R1.2
VSS: C1.2, C2.2, C3.2, C4.2, C5.2, C6.1, C7.1, C8.1, C9.1, C10.2, C11.2, C12.2, C13.1, C14.1, C15.1, C16.1, D1.3, D2.3, D3.3, D4.3, D5.3, D6.3, D7.3, D8.3, D9.3, D10.3, D11.3, D12.3, D13.3, D14.3, D15.3, D16.3, JP2.2, JP3.1, JP6.1, R4.1, R5.1

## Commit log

2015-02-14 added tabs1, license, readme
2015-02-20 fixed sensornode radio direction, power pin labels
2015-07-26 Added Sensor Node Model S, created board
2015-07-28 Finished Sensor Node Model S, created gerbers
2015-07-30 Added ESP8266-01 Tab
2015-10-02 Added v2
2016-01-31 added changes before switch to diptrace
2016-01-31 moved eagle files to eagle folder
2016-01-31 added diptrace folder
2016-02-06 Imported more boards into diptrace
2016-02-21 Created Sensornode S in Diptrace
2016-02-21 Fixed S v3 silkscreen, pour, other bits
2016-04-03 can't remember the last time I made a commit...
2016-04-03 cleaning...again?
2016-04-03 changed my mind, back to old organisation
2016-04-03 adding datasheet stuff
2016-04-03 testing github pages
2016-04-03 Init gh-pages
2016-04-03 testing gh-pages stuff.
2016-04-04 getting together gulpfile for docs
2016-04-04 Created index, docs publishing should work now
2016-04-04 cleaning out pages folder
2016-04-04 .gitignore should now work...
2016-08-30 Added new boards, can't remember which ones
2016-09-01 Dunno what's new. A datasheet snd stuff maybe.

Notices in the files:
parts and their libraries:
SparkFun-Connectors: Licensing: Creative Commons ShareAlike 4.0 International - https://creativecommons.org/licenses/by-sa/4.0
